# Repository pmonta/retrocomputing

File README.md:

# retrocomputing
Board- and chip-level reproductions of classic computing devices

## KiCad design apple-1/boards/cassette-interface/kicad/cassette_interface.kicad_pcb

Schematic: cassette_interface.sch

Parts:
C1: 0.1 uF; C_oval
D1: LED_ALT; LED
J1: APPLE1_EDGE
J2, J3: audio_jack; Jack_audio_3.5mm
Q1, Q2: Q_NPN_EBC; Transistor_NPN
R1: 100k; R_round
R2, R10: 100; R_round
R3, R4, R5, R6: 10k; R_oval
R7: 3k; R_round
R8: 47k; R_oval
R9: 10k; R_round
U1: 74LS02; DIP14
U2: 74LS10; DIP14
U3: LM311; DIP8
U4: 74LS74; DIP14
U5, U6: MMI6301; DIP16

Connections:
+5V: J1.22 (+5V), R2.1, R3.1, R5.1, R7.1, U1.14, U2.14, U3.8, U4.14, U5.16 (VCC), U6.16 (VCC)
-12V: J1.Z (-12V), U3.4
/A0: J1.W (A0), U2.9
/A1: J1.19 (A1), U5.6 (A1), U6.6 (A1)
/A2: J1.V (A2), U5.7 (A2), U6.7 (A2)
/A3: J1.18 (A3), U5.4 (A3), U6.4 (A3)
/A4: J1.U (A4), U5.3 (A4), U6.3 (A4)
/A5: J1.17 (A5), U5.2 (A5), U6.2 (A5)
/A6: J1.T (A6), U5.1 (A6), U6.1 (A6)
/A7: J1.16 (A7), U2.13, U5.15 (A7), U6.15 (A7)
/A8: J1.S (A8), U1.12
/A9: J1.15 (A9), U1.9
/A10: J1.R (A10), U1.8
/A11: J1.14 (A11), U1.3
/D0: J1.9 (D0), U5.12 (D0)
/D1: J1.J (D1), U5.11 (D1)
/D2: J1.8 (D2), U5.10 (D2)
/D3: J1.H (D3), U5.9 (D3)
/D4: J1.7 (D4), U6.12 (D0)
/D5: J1.F (D5), U6.11 (D1)
/D6: J1.6 (D6), U6.10 (D2)
/D7: J1.E (D7), U6.9 (D3)
/PHI2: J1.A (PHI2), U2.4
/PROM_A0: U1.4, U5.5 (A0), U6.5 (A0)
/PROM_CS_N: U1.11, U2.6, U5.13 (CS1_N), U5.14 (CS2_N), U6.13 (CS1_N), U6.14 (CS2_N)
/R: J1.21 (R), U1.2
GND: J1.20 (GND), J2.2 (ring), J3.2 (ring), Q2.1, R4.2, R6.2, R10.2, U1.7, U2.7, U3.1, U4.7, U5.8 (GND), U6.8 (GND)
unnamed: C1.1, R3.2, R4.1, U3.3
unnamed: C1.2, J2.1 (center), R1.2
unnamed: D1.1, Q1.3, Q2.3
unnamed: D1.2, R2.2
unnamed: J3.1 (center), R9.2, R10.1
unnamed: Q1.1, Q2.2
unnamed: Q1.2, R1.1
unnamed: R5.2, R6.1, R8.2, U3.2
unnamed: R7.2, R8.1, U2.1, U3.7
unnamed: R9.1, U4.5
unnamed: U1.1, U2.3
unnamed: U1.5, U1.6, U2.8
unnamed: U1.10, U2.5
unnamed: U1.13, U2.2, U4.3
unnamed: U2.10, U2.11, U2.12
unnamed: U4.2, U4.6

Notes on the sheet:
Apple-1 Cassette Interface
256x4 PROM
To Tape
From Tape

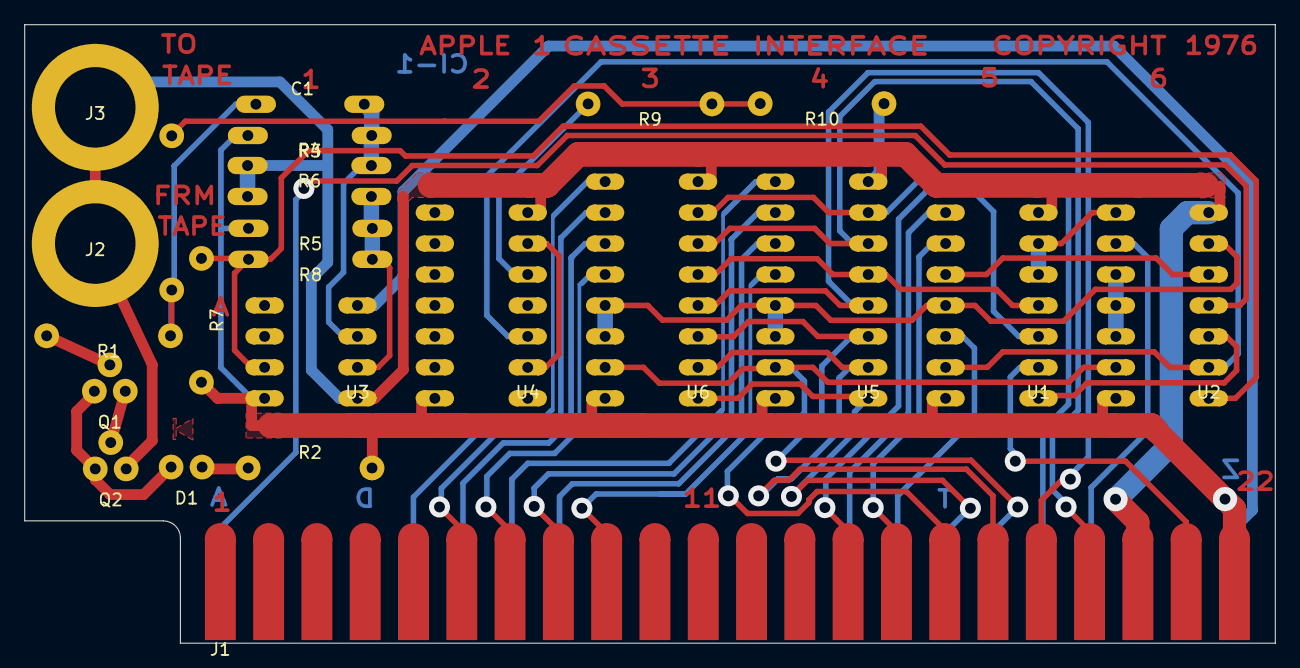
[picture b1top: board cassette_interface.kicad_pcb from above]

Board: 2 copper layers, 102.6 x 50.7 mm, 23 parts (0 on the bottom side), 43 nets.

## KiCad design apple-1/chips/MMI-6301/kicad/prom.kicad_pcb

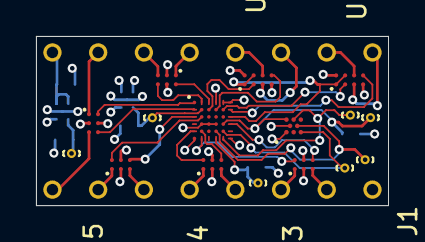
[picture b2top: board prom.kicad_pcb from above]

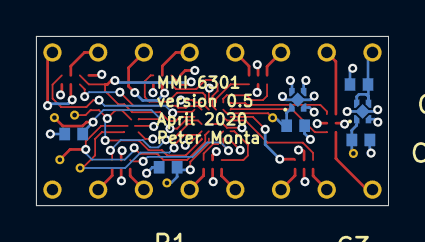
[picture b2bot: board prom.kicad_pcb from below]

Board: 4 copper layers, 19.6 x 9.4 mm, 24 parts (7 on the bottom side), 38 nets.

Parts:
C1, C2, C3: 1 uF; 0402
J1: DIP16_pins; flip-pins-DIP16
R1, R2: 10k; 0402
TP1, TP2, TP3, TP4, TP5, TP6, TP7: TestPoint_Alt; test-point
U1: TLV743P 3.3V; X2SON
U2: TLV743P 1.2V; X2SON
U3, U4, U5, U6, U7: 74LVC2G34; DSBGA-6
U8, U9: 74LVC2G125; DSBGA-8
U10: ICE40LP1K-CM36; ucBGA-36
U11: AT25DF041B; WLCSP-8

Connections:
+1V2: C3.1, TP2.1, U2.1, U10.B2
+3V3: C2.1, R1.1, R2.1, TP1.1, U1.1, U2.3, U2.4, U3.5, U4.5, U5.5, U6.5, U7.5, U8.A2, U9.A2, U10.A4, U10.A5, U10.A6, U10.F1, U10.F6, U11.A1
+5V: C1.1, J1.16, U1.3, U1.4
/Sheet5E85C2D6/DIP_A0: J1.5, U4.3
/Sheet5E85C2D6/DIP_A1: J1.6, U3.1
/Sheet5E85C2D6/DIP_A2: J1.7, U3.3
/Sheet5E85C2D6/DIP_A3: J1.4, U4.1
/Sheet5E85C2D6/DIP_A4: J1.3, U5.3
/Sheet5E85C2D6/DIP_A5: J1.2, U5.1
/Sheet5E85C2D6/DIP_A6: J1.1, U6.3
/Sheet5E85C2D6/DIP_A7: J1.15, U6.1
/Sheet5E85C2D6/DIP_CE1_N: J1.13, U7.1
/Sheet5E85C2D6/DIP_CE2_N: J1.14, U7.3
/Sheet5E85C2D6/DIP_D0: J1.12, U8.C2
/Sheet5E85C2D6/DIP_D1: J1.11, U8.C1
/Sheet5E85C2D6/DIP_D2: J1.10, U9.C2
/Sheet5E85C2D6/DIP_D3: J1.9, U9.C1
A0: U4.4, U10.E2
A1: U3.6, U10.F2
A2: U3.4, U10.D6
A3: U4.6, U10.E1
A4: U5.4, U10.C1
A5: U5.6, U10.C2
A6: U6.4, U10.B1
A7: U6.6, U10.A1
CE1_N: U7.6, U10.A3
CE2_N: U7.4, U10.A2
D0: U8.B1, U10.B3
D1: U8.D2, U10.B4
D2: U9.B1, U10.B5
D3: U9.D2, U10.B6
GND: C1.2, C2.2, C3.2, J1.8, U1.2, U1.TP, U2.2, U2.TP, U3.2, U4.2, U5.2, U6.2, U7.2, U8.D1, U9.D1, U10.D2, U10.D3, U10.D4, U11.B2
unnamed: R1.2, TP5.1, U10.F4
unnamed: R2.2, TP7.1, U10.D5, U11.A3
unnamed: TP3.1, U10.E4, U11.D2
unnamed: TP4.1, U10.F5, U11.C3
unnamed: TP6.1, U10.E5, U11.E1
OE_N: U8.A1, U8.B2, U9.A1, U9.B2, U10.C6

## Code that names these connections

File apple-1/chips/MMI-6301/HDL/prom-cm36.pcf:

set_io addr[0] E2
set_io addr[1] F2
set_io addr[2] D6
set_io addr[3] E1
set_io addr[4] C1
set_io addr[5] C2
set_io addr[6] B1
set_io addr[7] A1
set_io data[0] B3
set_io data[1] B4
set_io data[2] B5
set_io data[3] B6
set_io ce1_n   A3
set_io ce2_n   A2
set_io oe_n    C6

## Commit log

2020-03-19 Apple-1 cassette interface board
2020-03-19 Apple-1 PROM, 256x4
2020-03-24 add HDL models for Signetics 2504, 2519, 2513
2020-03-31 256x4 PROM: schematic, PCB footprints and placement
2020-04-03 MMI-6301 preliminary layout
2020-04-06 fold the rescued schematic symbols into the local library
2020-04-06 schematic cosmetic fixes
2020-04-06 completed layout
2020-04-06 library tweak
2020-04-07 minor layout updates: make vias partially tented (by postprocessing gerber files); redefine NSMD pads on the X2SON footprint; add silkscreen text
2020-04-08 make all symbols and footprints local; no silkscreen
2020-04-09 add polarity mark for LED1
2020-04-09 small layout tweaks for accuracy; use gerber X2; remove NPTH since there are none
